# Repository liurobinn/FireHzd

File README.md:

# FireHzd
Arduino based software for Flight Computer ```V6.0 APOGEE```. Also compatable with ```V4.0 Big Brain``` and ```V5.0 I Love Gravity```
# Include 
1. ```DMP``` output based on ```DMP6``` example code by Jeff Rowberg
2. ```BMP280``` output based on SparkFun examples.
3. Servo controling based on DMP output with PID filters involved.
4. Buzzer & Tri-Color LED control
5. ```.brd``` and ```.sch``` files for ```I Love Gravity``` and ```APOGEE```
6. ```.stl``` files for the TVC mount. The mount fits in ```3 inches``` body tube.

# Releases

- **1.0.0- first official pre-release of FireHzd flight software**

# Attention
```FireHzd``` is not certified for use in safety-critical applications. It should not be used in any life risking applications.

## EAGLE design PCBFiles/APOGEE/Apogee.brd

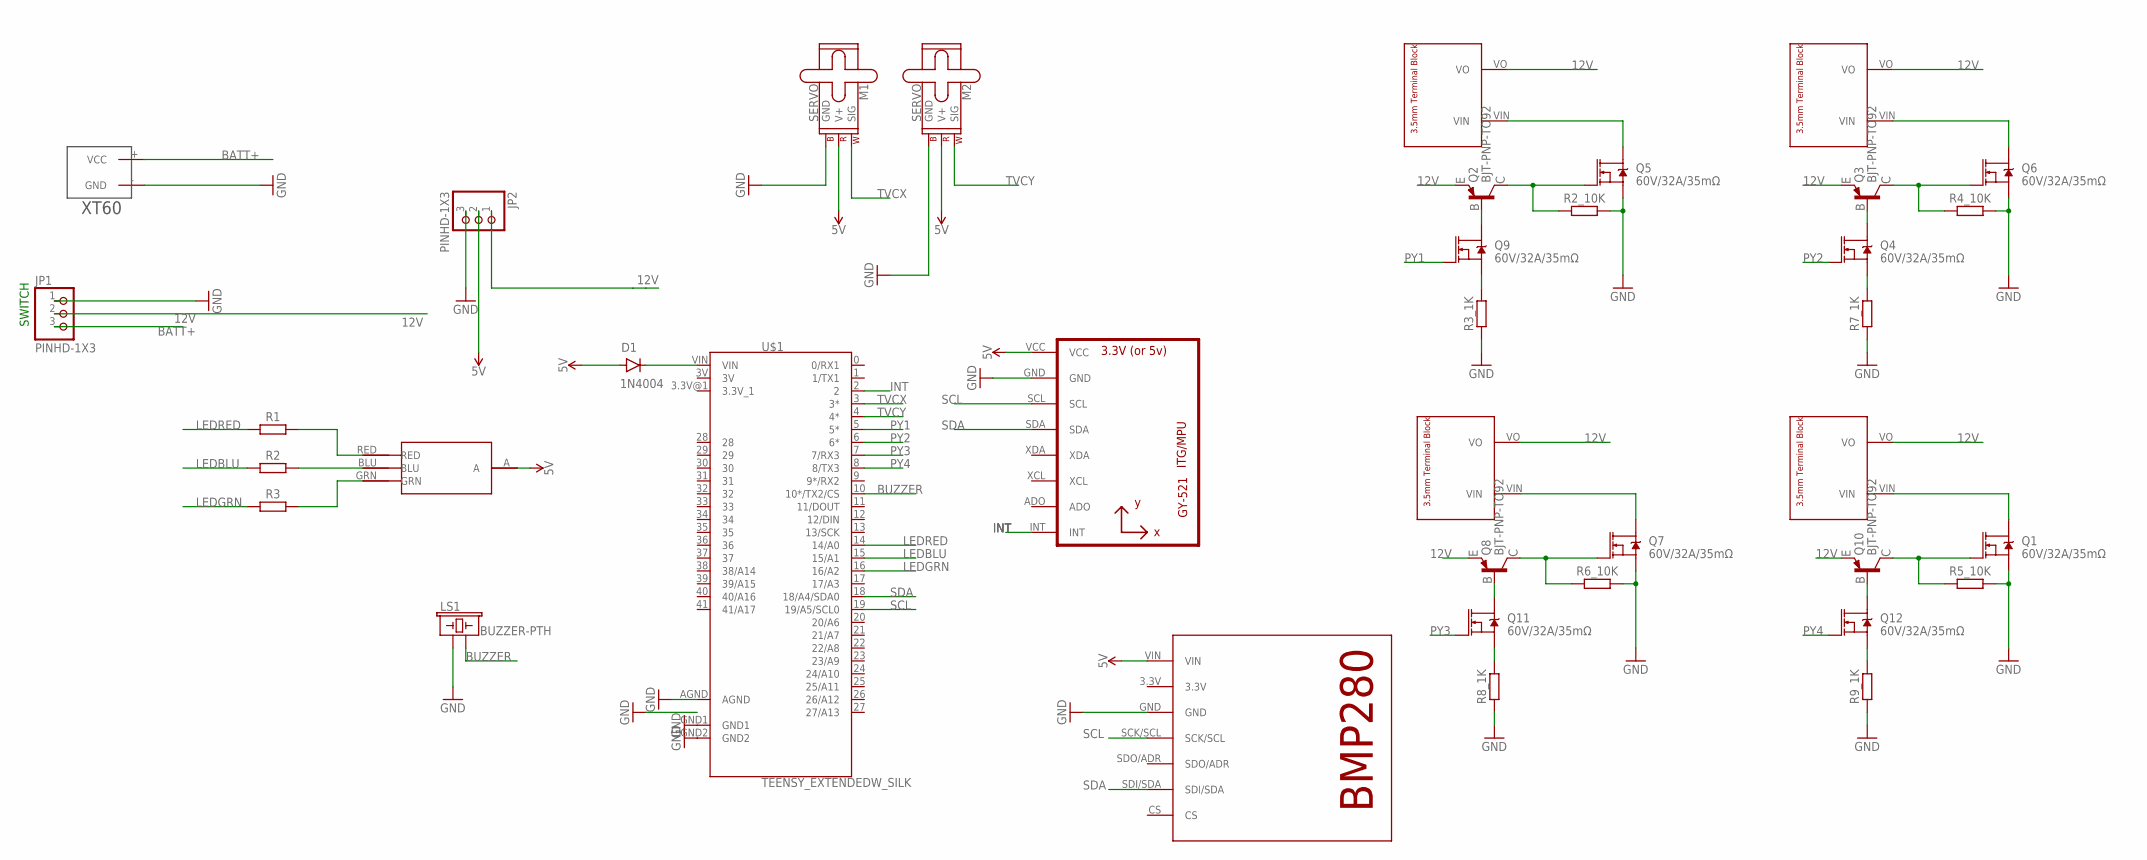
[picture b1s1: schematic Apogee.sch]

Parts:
D1: 1N4004; DO-41
JP1, JP2: PINHD-1X3; 1X03
LS1: BUZZER-PTH; BUZZER-12MM
M1, M2: SERVO; 1X03
Q1, Q4, Q5, Q6, Q7, Q9, Q11, Q12: 60V/32A/35mΩ; TO220V
Q2, Q3, Q8, Q10: BJT-PNP-TO92; TO92
R1, R2, R2_10K, R3, R3_1K, R4_10K, R5_10K, R6_10K, R7_1K, R8_1K, R9_1K: R_AXIAL-7.2MM-PITCH; RESAD724W46L381D178B
U1: GY-521MPU6050; GY-521
U$1: TEENSY_EXTENDEDW_SILK; TEENSY_EXTENDED
U$2: BMP280
U$3: XT60
U$4, U$6, U$9, U$10: TERMINALBLOCK
U$5: LEDCA

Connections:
3.3V_1: U$1.3.3V@1 (3.3V_1)
3V: U$1.3V
5V: D1.A, JP2.2, M1.2 (V+), M2.2 (V+), U1.VCC, U$2.VIN, U$5.A
12V: JP1.2, JP2.1, Q2.3 (E), Q3.3 (E), Q8.3 (E), Q10.3 (E), U$4.VO, U$6.VO, U$9.VO, U$10.VO
BATT+: JP1.3, U$3.+ (VCC)
BUZZER: LS1.- (2), U$1.10 (10*/TX2/CS)
GND: JP1.1, JP2.3, LS1.+ (1), M1.3 (GND), M2.3 (GND), Q1.3 (S), Q5.3 (S), Q6.3 (S), Q7.3 (S), R2_10K.2, R3_1K.1, R4_10K.2, R5_10K.2, R6_10K.2, R7_1K.1, R8_1K.1, R9_1K.1, U1.GND, U$1.GND1, U$1.GND2, U$2.GND, U$3.- (GND)
INT: U1.INT, U$1.2
LEDBLU: R2.1, U$1.15 (15/A1)
LEDGRN: R3.1, U$1.16 (16/A2)
LEDRED: R1.1, U$1.14 (14/A0)
unnamed: R3.2, U$5.GRN
unnamed: R2.2, U$5.BLU
unnamed: R1.2, U$5.RED
unnamed: Q1.2 (D), U$4.VIN
unnamed: D1.C, U$1.VIN
unnamed: Q5.2 (D), U$6.VIN
unnamed: Q2.2 (B), Q9.2 (D)
unnamed: Q6.2 (D), U$9.VIN
unnamed: Q7.2 (D), U$10.VIN
unnamed: Q9.3 (S), R3_1K.2
unnamed: Q7.1 (G), Q8.1 (C), R6_10K.1
unnamed: Q2.1 (C), Q5.1 (G), R2_10K.1
unnamed: Q1.1 (G), Q10.1 (C), R5_10K.1
unnamed: Q3.1 (C), Q6.1 (G), R4_10K.1
unnamed: Q11.3 (S), R8_1K.2
unnamed: Q12.3 (S), R9_1K.2
unnamed: Q4.3 (S), R7_1K.2
unnamed: Q3.2 (B), Q4.2 (D)
unnamed: Q8.2 (B), Q11.2 (D)
unnamed: Q10.2 (B), Q12.2 (D)
PY1: Q9.1 (G), U$1.5 (5*)
PY2: Q4.1 (G), U$1.6 (6*)
PY3: Q11.1 (G), U$1.7 (7/RX3)
PY4: Q12.1 (G), U$1.8 (8/TX3)
SCL: U1.SCL, U$1.19 (19/A5/SCL0), U$2.SCK/SCL
SDA: U1.SDA, U$1.18 (18/A4/SDA0), U$2.SDI/SDA
TVCX: M1.1 (SIG), U$1.3 (3*)
TVCY: M2.1 (SIG), U$1.4 (4*)

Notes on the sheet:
SWITCH

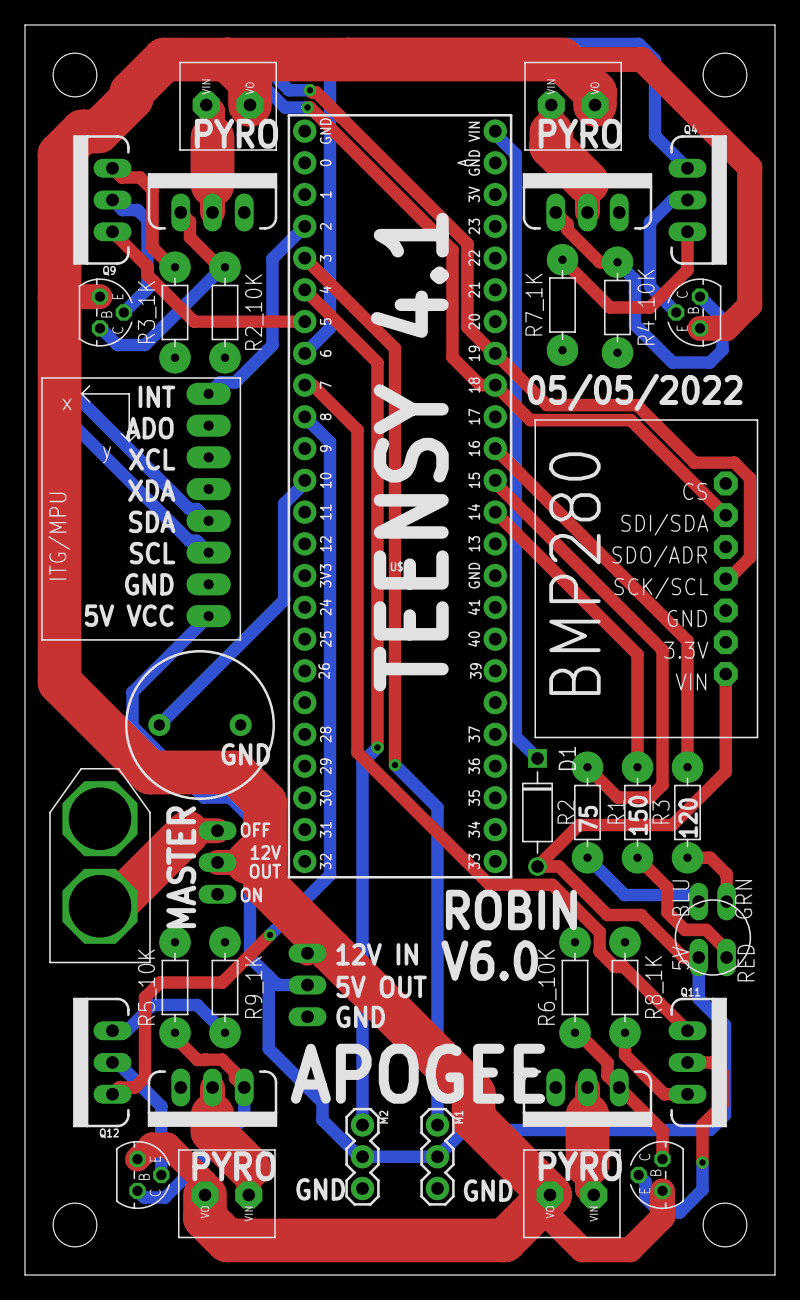
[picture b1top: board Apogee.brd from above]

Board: 2 copper layers, 60.0 x 100.0 mm, 38 parts (0 on the bottom side), 37 nets.

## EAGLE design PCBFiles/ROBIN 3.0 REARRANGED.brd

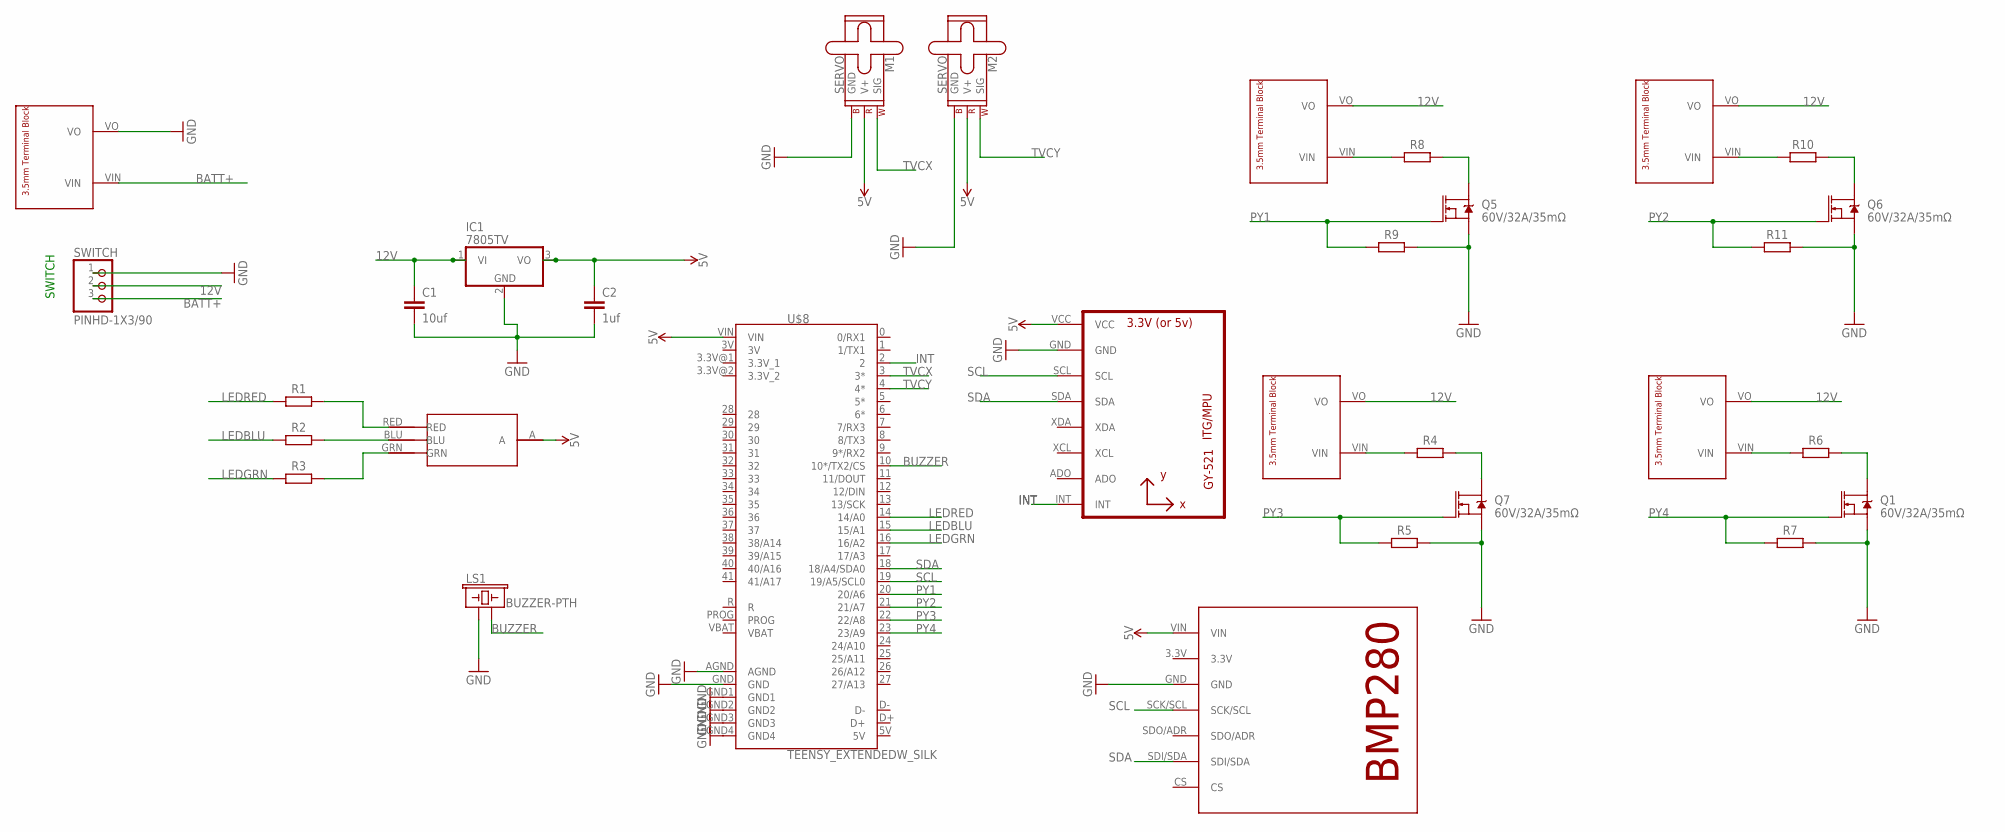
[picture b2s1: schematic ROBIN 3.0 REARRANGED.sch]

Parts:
C1: 10uf; CAP-PTH-2.54
C2: 1uf; CAP-PTH-2.54
IC1: 7805TV; TO220V
LS1: BUZZER-PTH; BUZZER-12MM
M1, M2: SERVO; 1X03
Q1, Q5, Q6, Q7: 60V/32A/35mΩ; TO220V
R1, R2, R3, R4, R5, R6, R7, R8, R9, R10, R11: R_AXIAL-7.2MM-PITCH; RESAD724W46L381D178B
SWITCH: PINHD-1X3/90; 1X03/90
U1: GY-521MPU6050; GY-521
U$1, U$4, U$6, U$9, U$10: TERMINALBLOCK
U$2: BMP280
U$7: LEDCA
U$8: TEENSY_EXTENDEDW_SILK; TEENSY_EXTENDED

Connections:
3.3V_1: U$8.3.3V@1 (3.3V_1)
3.3V_2: U$8.3.3V@2 (3.3V_2)
3V: U$8.3V
5V: C2.1, IC1.3 (VO), M1.2 (V+), M2.2 (V+), U1.VCC, U$2.VIN, U$7.A, U$8.5V, U$8.VIN
12V: C1.1, IC1.1 (VI), SWITCH.2, U$4.VO, U$6.VO, U$9.VO, U$10.VO
BATT+: SWITCH.3, U$1.VIN
BUZZER: LS1.- (2), U$8.10 (10*/TX2/CS)
D+: U$8.D+
D-: U$8.D-
GND: C1.2, C2.2, IC1.2 (GND), LS1.+ (1), M1.3 (GND), M2.3 (GND), Q1.3 (S), Q5.3 (S), Q6.3 (S), Q7.3 (S), R5.2, R7.2, R9.2, R11.2, SWITCH.1, U1.GND, U$1.VO, U$2.GND, U$8.AGND, U$8.GND, U$8.GND1, U$8.GND2, U$8.GND3, U$8.GND4
INT: U1.INT, U$8.2
LEDBLU: R2.1, U$8.15 (15/A1)
LEDGRN: R3.1, U$8.16 (16/A2)
LEDRED: R1.1, U$8.14 (14/A0)
unnamed: R3.2, U$7.GRN
unnamed: R2.2, U$7.BLU
unnamed: R1.2, U$7.RED
unnamed: R6.1, U$4.VIN
unnamed: Q1.2 (D), R6.2
unnamed: R8.1, U$6.VIN
unnamed: Q5.2 (D), R8.2
unnamed: R10.1, U$9.VIN
unnamed: Q6.2 (D), R10.2
unnamed: R4.1, U$10.VIN
unnamed: Q7.2 (D), R4.2
PY1: Q5.1 (G), R9.1, U$8.20 (20/A6)
PY2: Q6.1 (G), R11.1, U$8.21 (21/A7)
PY3: Q7.1 (G), R5.1, U$8.22 (22/A8)
PY4: Q1.1 (G), R7.1, U$8.23 (23/A9)
SCL: U1.SCL, U$2.SCK/SCL, U$8.19 (19/A5/SCL0)
SDA: U1.SDA, U$2.SDI/SDA, U$8.18 (18/A4/SDA0)
TVCX: M1.1 (SIG), U$8.3 (3*)
TVCY: M2.1 (SIG), U$8.4 (4*)
VBAT: U$8.VBAT

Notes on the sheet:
SWITCH

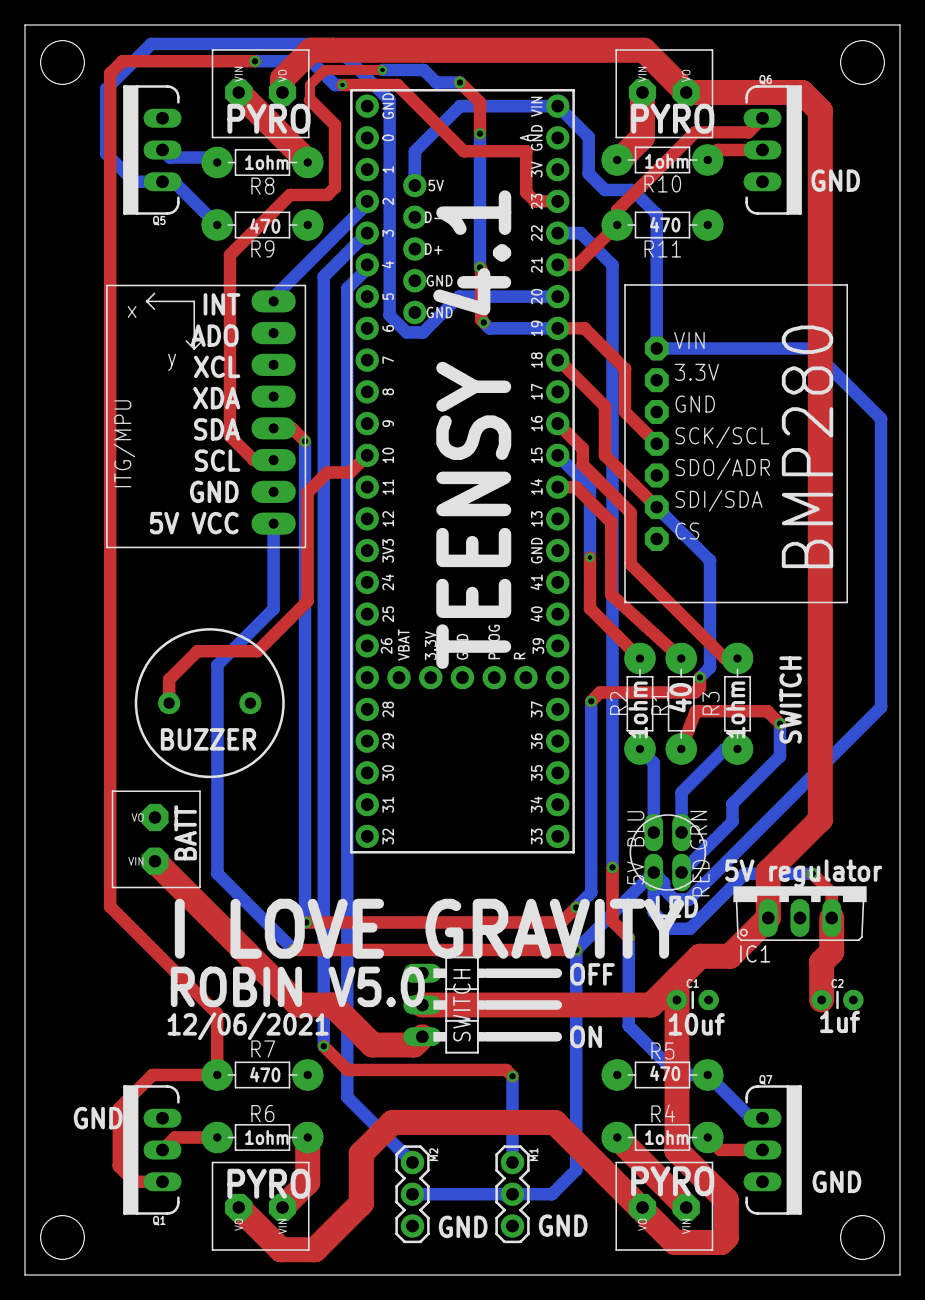
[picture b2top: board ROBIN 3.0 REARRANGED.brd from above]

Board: 2 copper layers, 70.0 x 100.0 mm, 31 parts (0 on the bottom side), 28 nets.

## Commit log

2022-01-20 Add existing file
2022-01-20 Change File name
2022-01-20 test
2022-01-21 test upload
2022-01-21 upload pic
2022-01-28 cleaned up the code
2022-01-29 commit to main
2022-02-06 Thrust Vector Control
2022-02-08 Commit to master
2022-02-10 Added PID
2022-03-23 Parametric Code for tvc
2022-04-15 Added platfrom IO
2022-04-15 testing!!!
2022-04-15 Updated PID and offsets
2022-04-15 Added comments
2022-04-17 test upload from macbook 2017
2022-04-17 sucess
2022-04-17 PID issue, see comments
2022-04-17 PID issue; see comments
2022-04-22 fixed pid issue
2022-05-05 comments
2022-05-12 library for gravitational potential energy
2022-05-23 Update PCB
2022-06-05 Added Launch Detection, but need to verify the axis
2024-03-07 show amanda how stuff works
2024-03-07 second attempt
2024-03-07 cleaned up

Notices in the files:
parts and their libraries:
SparkFun-Electromechanical: Licensing: Creative Commons ShareAlike 4.0 International - https://creativecommons.org/licenses/by-sa/4.0
